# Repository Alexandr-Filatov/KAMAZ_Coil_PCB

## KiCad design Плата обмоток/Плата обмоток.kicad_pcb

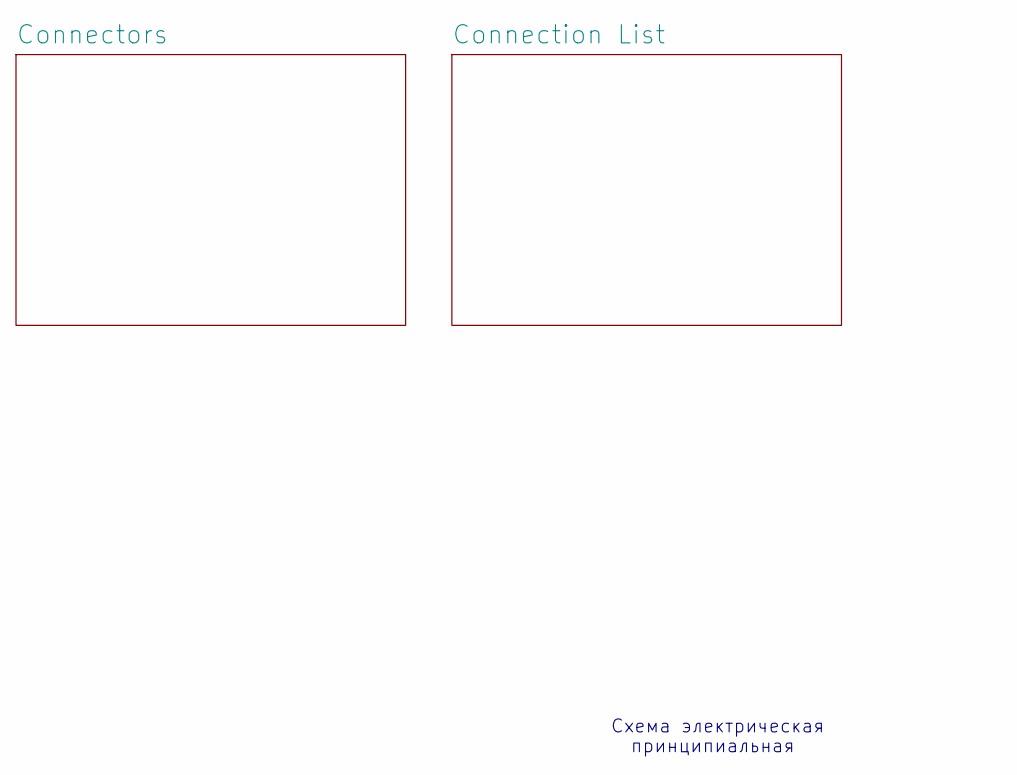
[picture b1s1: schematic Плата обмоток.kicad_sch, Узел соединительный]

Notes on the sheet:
принципиальная
Схема электрическая

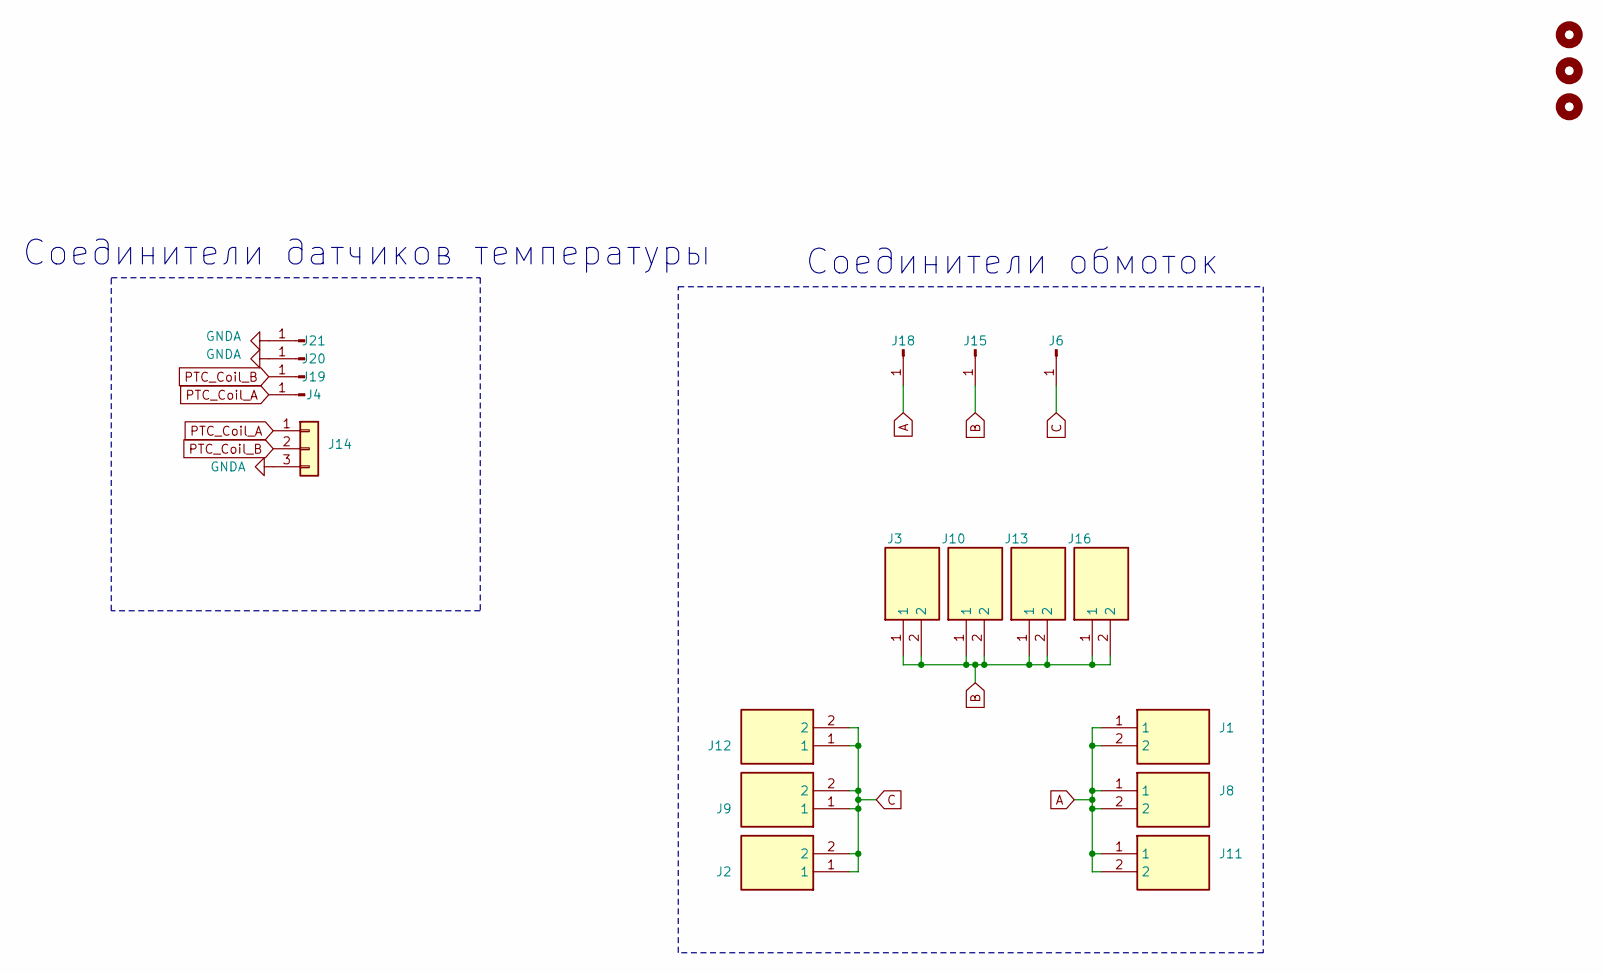
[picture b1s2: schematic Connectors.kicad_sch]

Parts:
H1, H2, H3: MountingHole; MountingHole_3.2mm_M3
J1, J2, J3, J8, J9, J10, J11, J12, J13, J16: 4900; 3551; Manufacturer_Part_Number 4900; Mouser Part Number 534-4900
J4, J19, J20, J21: B1; temp_wire
J6: A1; KFS2-M3
J14: Conn_01x03; PinSocket_1x03_P2.54mm_Vertical
J15: C1; KFS2-M3
J18: B1; KFS2-M3

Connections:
A: J1.1, J1.2, J8.1, J8.2, J11.1, J11.2, J18.1
B: J3.1, J3.2, J10.1, J10.2, J13.1, J13.2, J15.1, J16.1, J16.2
C: J2.1, J2.2, J6.1, J9.1, J9.2, J12.1, J12.2
GNDA: J14.3, J20.1, J21.1
PTC_Coil_A: J4.1, J14.1
PTC_Coil_B: J14.2, J19.1

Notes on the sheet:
Соединители датчиков температуры
Соединители обмоток

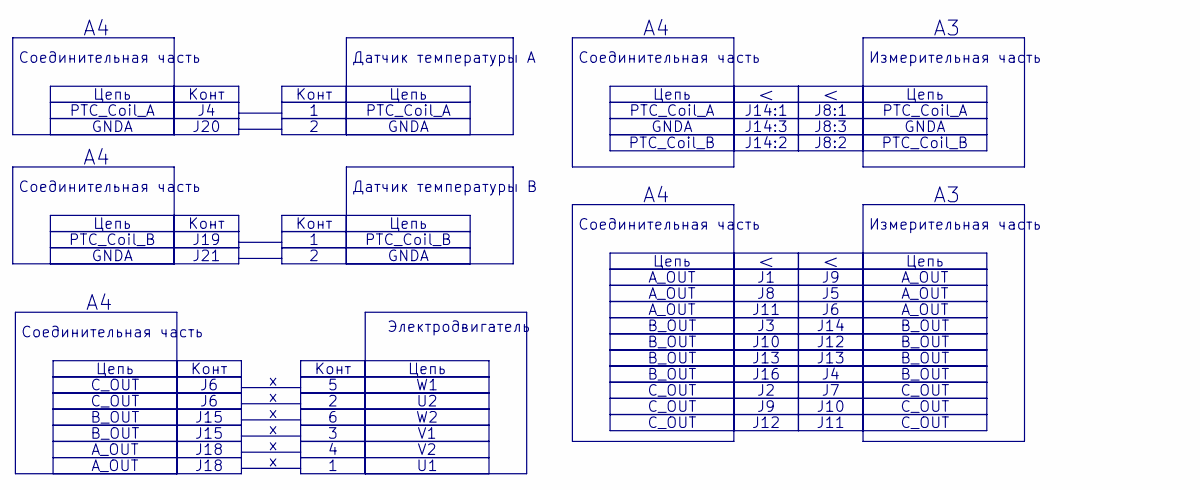
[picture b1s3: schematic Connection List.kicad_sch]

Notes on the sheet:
Цепь
A_OUT
J11
J18
PTC_Coil_A
J12
GNDA
J13
C_OUT
J15
С_OUT
J14
J18
Конт
PTC_Coil_B
J10
B_OUT
J14:2
J20
J10
J14:3
J12
J8:2
J19
J8:3
J14:1
J8:1
J16
J21
Датчик температуры B
Соединительная часть
Измерительная часть
Датчик температуры А
Электродвигатель

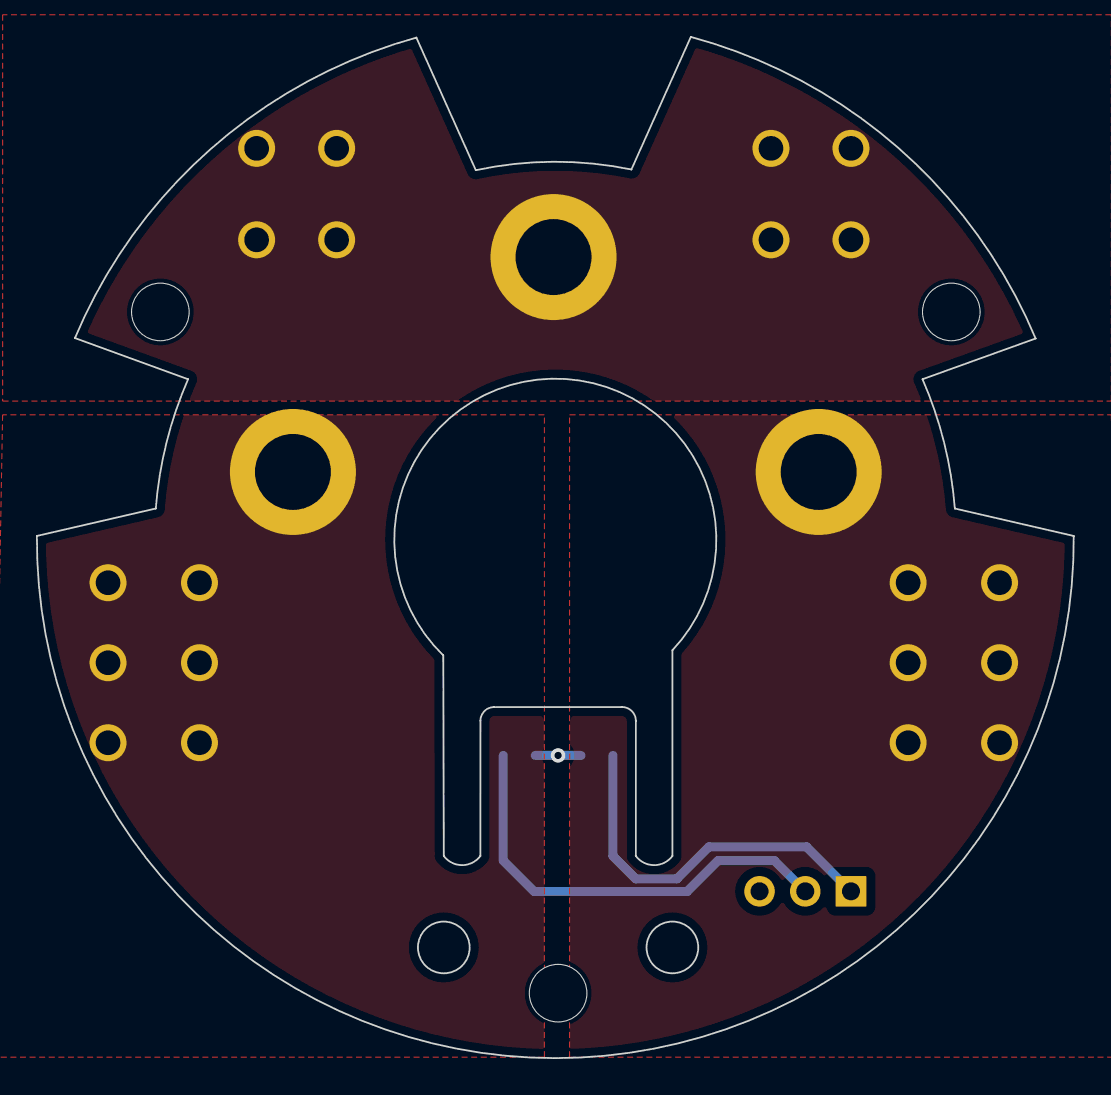
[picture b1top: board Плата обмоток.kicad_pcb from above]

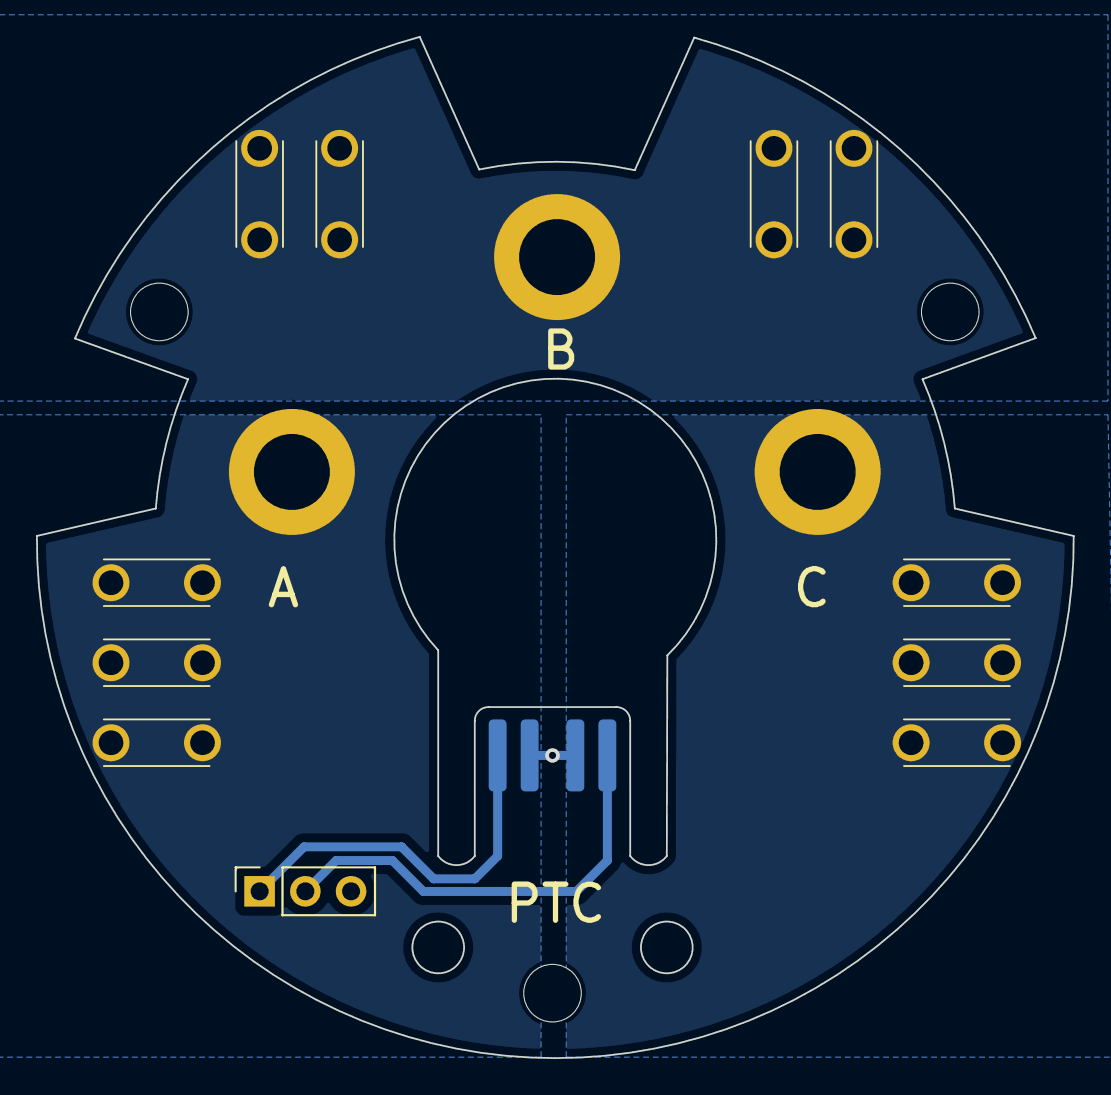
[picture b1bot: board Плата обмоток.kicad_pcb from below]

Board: 4 copper layers, 57.6 x 56.7 mm, 21 parts (18 on the bottom side), 6 nets.

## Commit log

2023-12-05 Первый вариант платы
2023-12-07 Добавил ножевые разъёмы
2023-12-11 Прямой вывод обмоток на плату
2023-12-11 Расставил ножевые разъёмы финально
2023-12-12 Финальная доработка
2023-12-12 Ещё доработать
2023-12-14 Собираю документацию
2023-12-17 Добавил все документы
2023-12-23 Версия под отчётность
2024-08-01 VER2.0
2024-08-05 Базовый вариант с пайкой
2024-08-05 Вариант с запресованной гайкой и обжатыми проводами
2024-08-12 VER1.0
2024-08-12 Сделал Т-образный вырез
2024-09-30 Добавил модель плты
2024-10-01 Добавил все в BOM
2024-10-02 Отправил на проверку в резонит
2024-12-02 Изменения: добавил папку с отчетностью
